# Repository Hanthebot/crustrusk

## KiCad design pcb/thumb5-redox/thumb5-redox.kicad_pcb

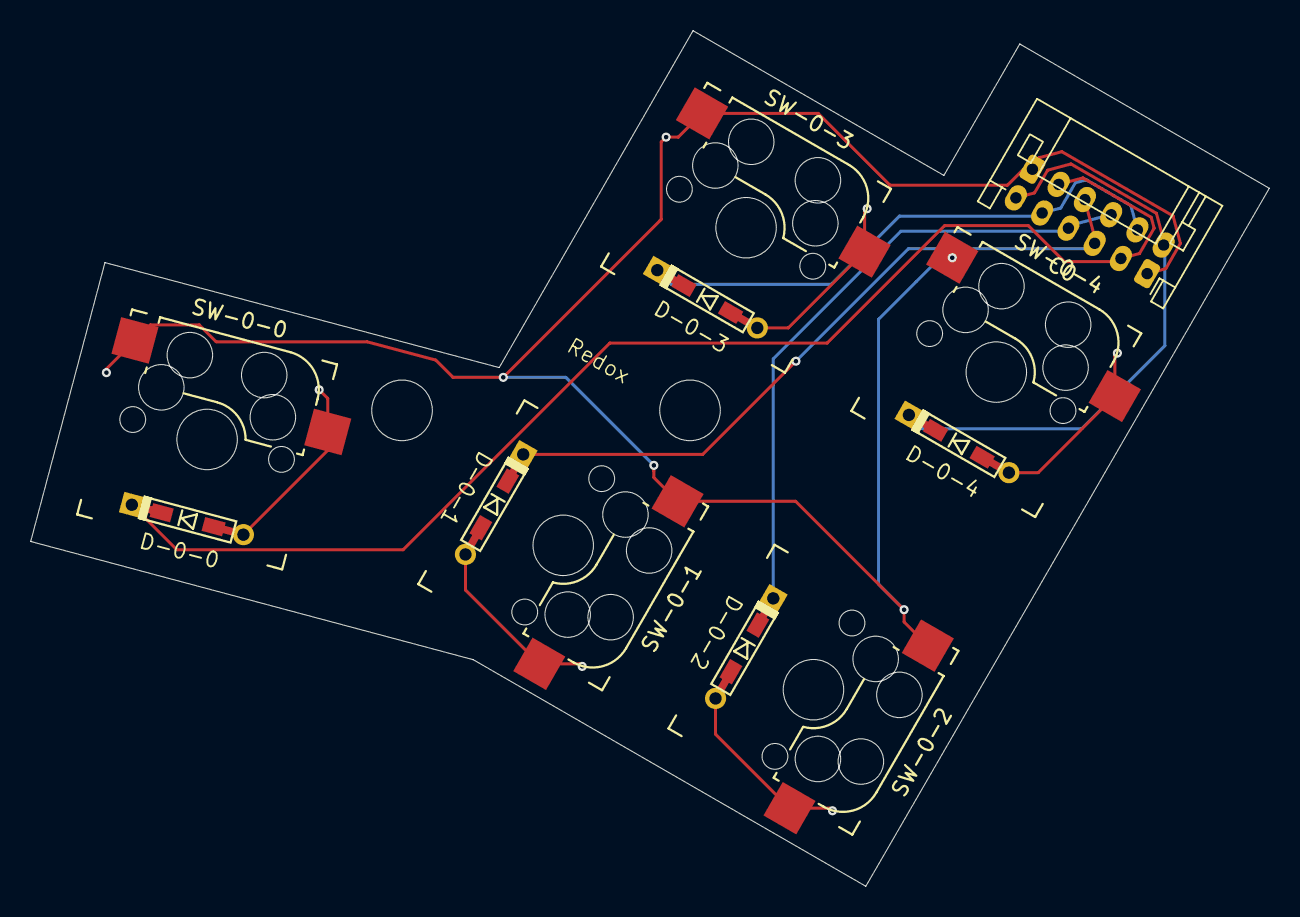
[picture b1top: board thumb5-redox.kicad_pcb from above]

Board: 2 copper layers, 81.7 x 56.5 mm, 11 parts (0 on the bottom side), 11 nets.

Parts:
C0: Conn_01x06_Socket; reversible JST_PH_S6B-PH-K_1x06_P2.00mm_Horizontal
D-0-0, D-0-1, D-0-2, D-0-3, D-0-4: D; Diode_TH_SMD_REVERSIBLE
SW-0-0, SW-0-1, SW-0-2, SW-0-3, SW-0-4: SW_Push; Kailh_hotswap_only_socket_MX_optional_reversible-MIRROR

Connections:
COL0: C0.1, SW-0-0.2, SW-0-1.2, SW-0-2.2, SW-0-3.2, SW-0-4.2
unnamed: D-0-0.2 (A), SW-0-0.1
unnamed: D-0-1.2 (A), SW-0-1.1
unnamed: D-0-2.2 (A), SW-0-2.1
unnamed: D-0-3.2 (A), SW-0-3.1
unnamed: D-0-4.2 (A), SW-0-4.1
ROW0-0: C0.2, D-0-0.1 (K)
ROW1-0: C0.3, D-0-1.1 (K)
ROW2-0: C0.4, D-0-2.1 (K)
ROW3-0: C0.5, D-0-3.1 (K)
ROW4-0: C0.6, D-0-4.1 (K)
